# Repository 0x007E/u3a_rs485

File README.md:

# `U3A_rs485` - RS485 - Adapter for U3A

The `U3A_rs485` project is based on a ([THVD1452](#additional-information)) that ist used to change the RX/TX signals to the required differential signal level of TIA/TIA-485-A standard. It can simply be adapted to the [U3A-Module](https://github.com/0x007e/u3a).

> To use it with a [DSUB](https://www.reichelt.at/at/de/shop/produkt/d-sub_stecker_9_polig-342342) connector it is necessary to solder a connection cable to the DSUB that can be connected with the screw terminal.

| Experience | Level |
|:------------|:-----:|
| Soldering   |  |
| Mechanical  |  |

# Downloads

| Type       | File               | Description              |
|:----------:|:------------------:|:-------------------------|
| Schematic  | [pdf](https://github.com/0x007E/u3a_rs485/releases/latest/download/schematic.pdf) / [cadlab](https://cadlab.io/project/29763/main/files) | Schematic files |
| Board      | [pdf](https://github.com/0x007E/u3a_rs485/releases/latest/download/pcb.pdf) / [cadlab](https://cadlab.io/project/29763/main/files) | Board file |
| Drill      | [pdf](https://github.com/0x007E/u3a_rs485/releases/latest/download/drill.pdf) | Drill file |
| BoM | [xlsx](https://github.com/0x007E/u3a_rs485/releases/latest/download/bom.xlsx) / [html](https://github.com/0x007E/u3a_rs485/releases/latest/download/ibom.html)          | Bill of Material as Excel/interactive HTML |
| PCB    | [zip](https://github.com/0x007E/u3a_rs485/releases/latest/download/kicad.zip) / [tar](https://github.com/0x007E/u3a_rs485/releases/latest/download/kicad.tar.gz)    | KiCAD/Gerber/BoM/Drill files       |
| Mechanical | [zip](https://github.com/0x007E/u3a_rs485/releases/latest/download/freecad.zip) / [tar](https://github.com/0x007E/u3a_rs485/releases/latest/download/freecad.tar.gz) | FreeCAD/Housing and PCB (STEP/STL) files     |

# Hardware

There are two parts of the hardware. The pcb and the housing of the `U3A_rs485`. The pcb is created with [KiCAD](#additional-information) and the housing with [FreeCAD](#additional-information). All files are built with `github actions` so that they are ready for a production environment. The housing is printed with a 3D-printer (`Dremel 3D40`).

## PCB

The circuit board is populated on both sides (Top, Bottom). The best way for soldering the `SMD` components is within a vapor phase soldering system and for the `THT` components with a standard soldering system.

### Top Layer

### Bottom Layer

## Mechanical

The housing has a tolerance of `0.2mm` on each side of the case. So the pcb should fit perfectly in the housing. The tolerance can be modified with `FreeCAD` in the `Parameter` Spreadsheet.

### Assembled

### Exploded

# Connection/Setup

The `U3A_rs485` is powerd over the `U3A` board with `5V`. The voltage of the pins are driven by a `THVD1452` for data transmission that meets the TIA/TIA-485-A standard.

## Simple loopback setup for testing purpose

``` bash
#
#            +-----------------------------------+           +-----------------------------------+      +---------------------+
#            |                                 J2|           |J2     U                       +---+---+  |                     |
#            | J1         U3A_rs485           +--+--+     +--+--+    S                U      |  USB  |--+ +-----------------+ |
#         +--+--+                             | VCC +-----+ VCC |    B      UPDI      3      +---+---+  | | TeraTerm        | |
#         + VCC |            T +---+          | GND +-----+ GND |    /    +---+---+   A          |      | | ~~~~~~~~        | |
#         +-----+            E | X | J        |  X  +-----| PDI |    U    |   |   |              |      | | ~~~~~           | |
#   L +---+  A  |            R | X | 3        | CTS +-----+ CTS |    A    |   |   |              |      | | ~~~~~~~~~~~~    | |
#   O | +-+  B  |            M +---+          | RTS +-----+ RTS |    R    | X | X |              |      | |                 | |
#   O +-|-+  Y  |    ~       . | X | J        | TXD +-----+ TXD |    T    +---+---+     +-+      |      | +-----------------+ |
#   P   +-+  Z  |    P   T   1 | X | 5        | RXD +-----+ RXD |    /                 / /       |      |                     |
#   B     +-----+    W   X   2 +---+          +--+--+     +--+--+    U               +-+-+-+-+-+-+      | Computer            |
#   A     + GND |    R   D   0                   |           |       P               | 5V  | 3V3 |      |                     |
#   C     +--+--+    E   E   Ω                   |           |       D               +-----+-----+      +---------------------+
#   K        |       N   N                       |           |       I         J4                |
#            | +---+---+---+---+---+---+---+---+ |           | +---+---+---+---+---+---+---+---+ |
#            | | V | C | C | D | D | D | R | G | |           | | V | C | C | D | D | D | R | G | |
#            +-+ C | B | B | C | T | C | I | N +-+           +-+ C | B | B | C | T | C | I | N +-+
#              | C | 3 | 2 | D | R | R |   | D |               | C | 3 | 2 | D | R | R |   | D |
#              +---+-+-+-+-+---+---+---+---+---+               +---+-+-+-+-+---+---+---+---+---+
#                    |   |                                           |   |
#                    |   +-------------------------------------------|---+
#                    +-----------------------------------------------+
```

# Additional Information

| Type       | Link                                                  | Description                                          |
|:----------:|:-----------------------------------------------------:|:-----------------------------------------------------|
| THVD1452   | [pdf](https://www.ti.com/lit/ds/symlink/thvd1452.pdf) | UART / RS485 level converter                         |
| KiCAD      | [web](https://www.kicad.org/)                         | KiCAD project page                                   |
| FreeCAD    | [web](https://www.freecad.org/)                       | FreeCAD project page                                 |

---

R. GAECHTER

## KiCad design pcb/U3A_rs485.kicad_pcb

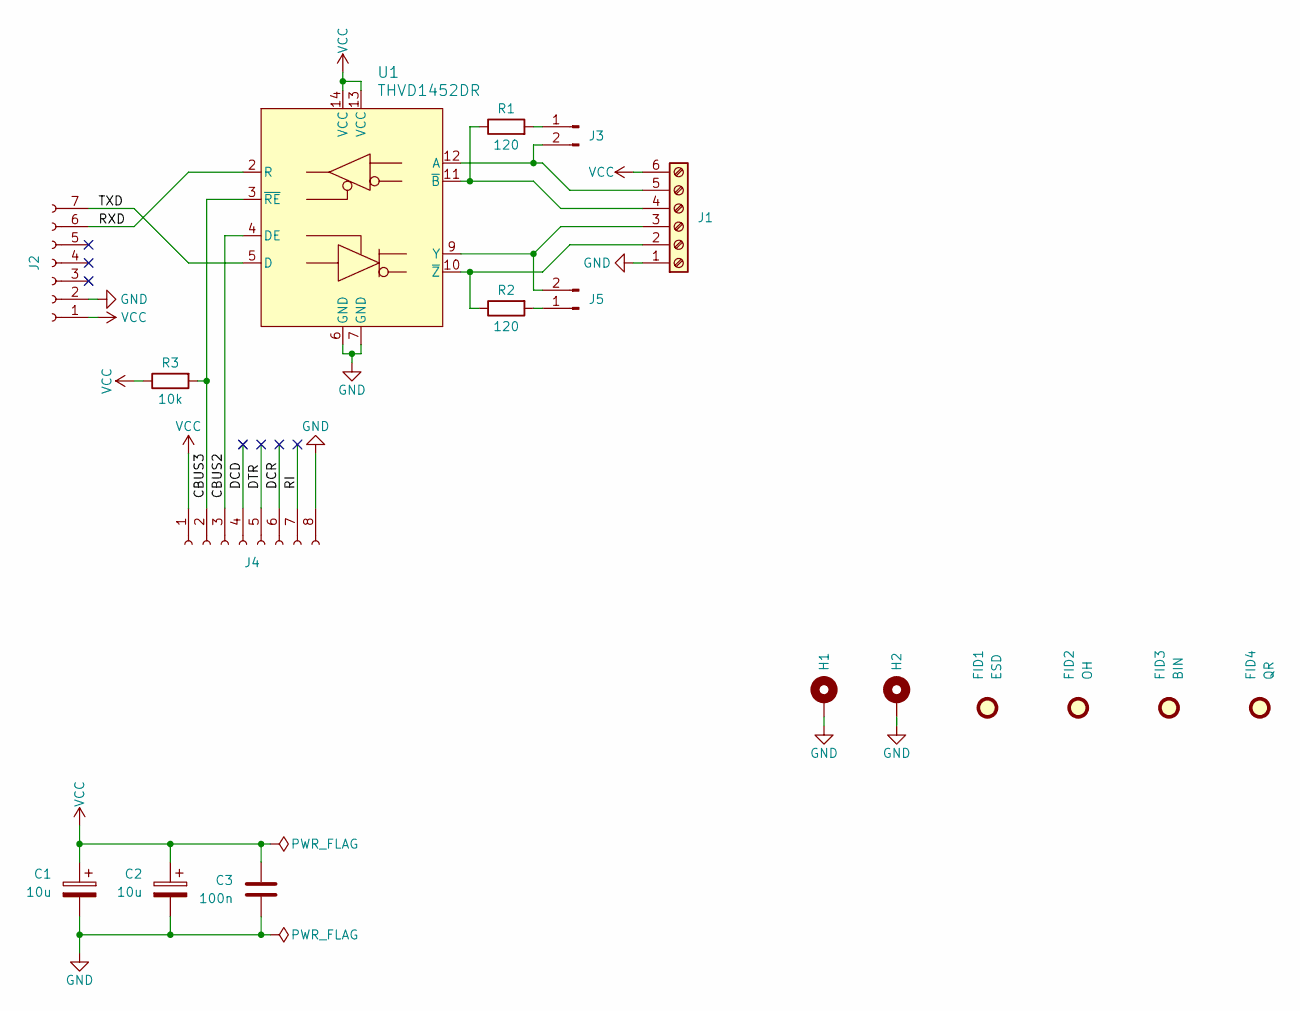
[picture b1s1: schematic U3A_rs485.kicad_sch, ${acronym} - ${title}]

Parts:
C1, C2: 10u; CP_EIA-6032-28_Kemet-C
C3: 100n; C_1206_3216Metric
FID1: ESD; ESD-Logo_6.6x6mm_SilkScreen
FID2: OH; OSHW-Logo_5.7x6mm_SilkScreen
FID3: BIN; WEEE-Logo_4.2x6mm_SilkScreen
FID4: QR; QR_0x007e
H1, H2: MountingHole_Pad; MountingHole_2.7mm_M2.5_Pad
J1: Screw_Terminal_01x06; TerminalBlock_Phoenix_PT-1,5-6-3.5-H_1x06_P3.50mm_Horizontal
J2: Conn_01x07_Socket; PinSocket_1x07_P2.54mm_Vertical
J3, J5: Conn_01x02_Pin; PinHeader_1x02_P2.54mm_Vertical
J4: Conn_01x08_Socket; PinSocket_1x08_P2.54mm_Vertical
R1, R2: 120; R_1206_3216Metric
R3: 10k; R_1206_3216Metric
U1: THVD1452DR; SOIC-14_3.9x8.7mm_P1.27mm

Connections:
/CBUS2: J4.3, U1.4 (DE)
/CBUS3: J4.2, R3.2, U1.3 (~RE)
/DCD: J4.4
/DCR: J4.6
/DTR: J4.5
/RI: J4.7
/RXD: J2.6, U1.2 (R)
/TXD: J2.7, U1.5 (D)
GND: C1.2, C2.2, C3.1, H1.1, H2.1, J1.1, J2.2, J4.8, U1.6 (GND), U1.7 (GND)
unnamed: J1.2, R2.1, U1.10 (~Z)
unnamed: J1.3, J5.2, U1.9 (Y)
unnamed: J1.4, R1.1, U1.11 (~B)
unnamed: J1.5, J3.2, U1.12 (A)
unnamed: J3.1, R1.2
unnamed: J5.1, R2.2
VCC: C1.1, C2.1, C3.2, J1.6, J2.1, J4.1, R3.1, U1.13 (VCC), U1.14 (VCC)

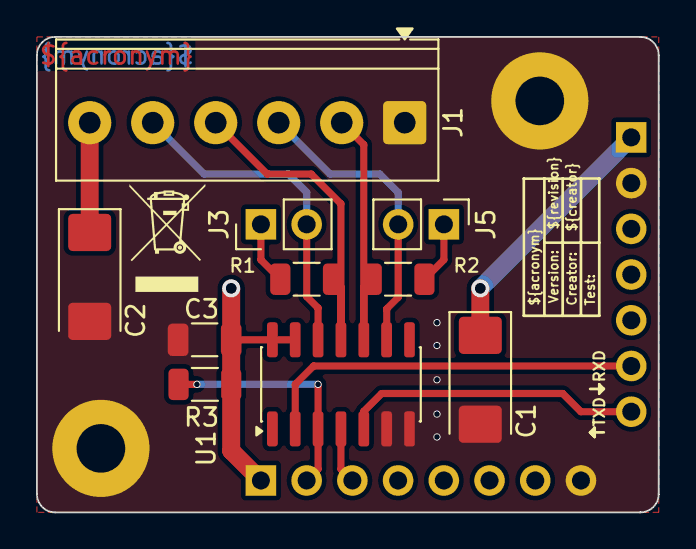
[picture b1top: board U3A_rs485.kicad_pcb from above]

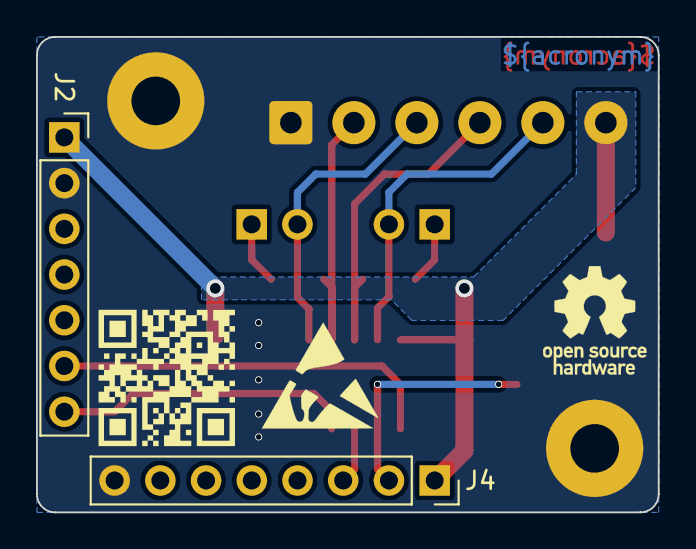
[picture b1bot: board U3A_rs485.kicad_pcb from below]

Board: 2 copper layers, 34.5 x 26.4 mm, 18 parts (5 on the bottom side), 12 nets.

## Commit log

2025-11-22 Add pcb layout
2025-11-22 Add mechanical parts
2025-11-23 Add vendor-ids to devices
2025-11-23 Add assembly explosion
2025-11-23 Add missing pull-up resistor
2025-11-23 Add build pipeline
2025-11-23 Add release pipeline
2025-11-23 Add README.md
2025-11-23 Fix connection setup ascii graphic
2025-11-24 Update THVD1452 symbol color
2025-11-25 Add deepwiki badge
2025-11-26 Change vendor of parts
2025-12-10 Move pcb to part
2026-06-19 Update to KiCAD 9
2026-06-19 Rename/Add/Remove bom fields
2026-06-19 Update build pipeline
2026-06-19 Update release pipeline
2026-06-19 Add thumbnail creation
2026-06-22 Adapt output filenames
2026-06-22 Add missing values in bom
2026-06-22 Adapt config and update action versions
2026-06-22 Fix freecad path issue

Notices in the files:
README.md:
License CC By-NC-SA
parts and their libraries:
license: CC BY-NC-SA 4.0
